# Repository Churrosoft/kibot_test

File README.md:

# kibot_test

export KICAD6_3DMODEL_DIR="/usr/share/kicad/3dmodels/"
export KICAD6_FOOTPRINT_DIR="/usr/share/kicad/footprints/"
export KICAD6_SYMBOL_DIR="/usr/share/kicad/symbols/"
export KICAD6_TEMPLATE_DIR="/usr/share/kicad/template/"

KICAD_USER_TEMPLATE_DIR	/home/fdsoftware/.local/share/kicad/6.0/template/	

KICAD6_3RD_PARTY	/home/fdsoftware/.local/share/kicad/6.0/3rdparty

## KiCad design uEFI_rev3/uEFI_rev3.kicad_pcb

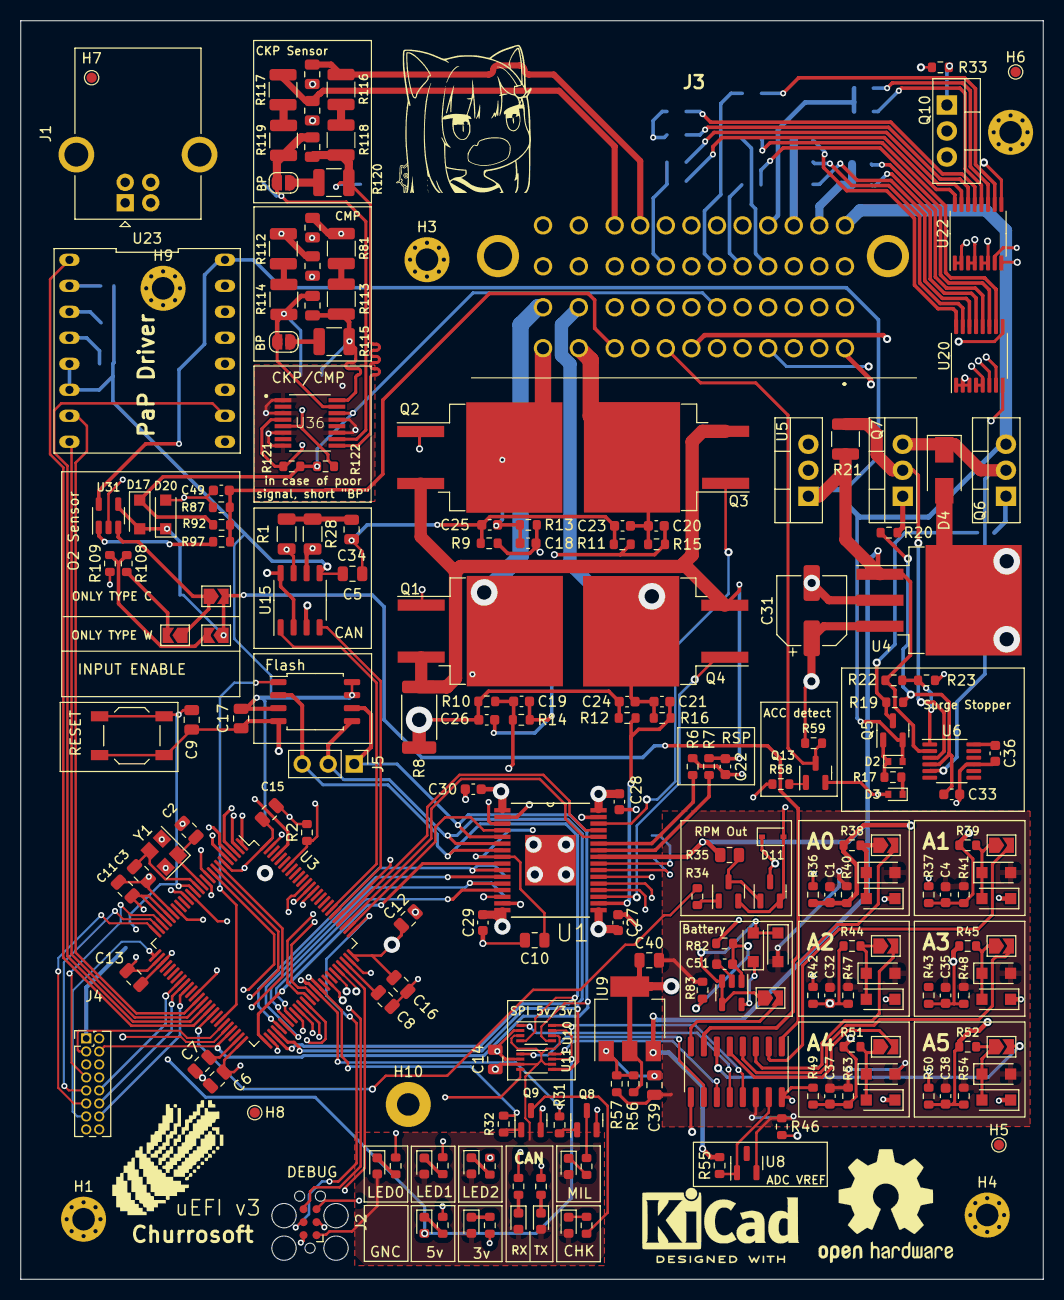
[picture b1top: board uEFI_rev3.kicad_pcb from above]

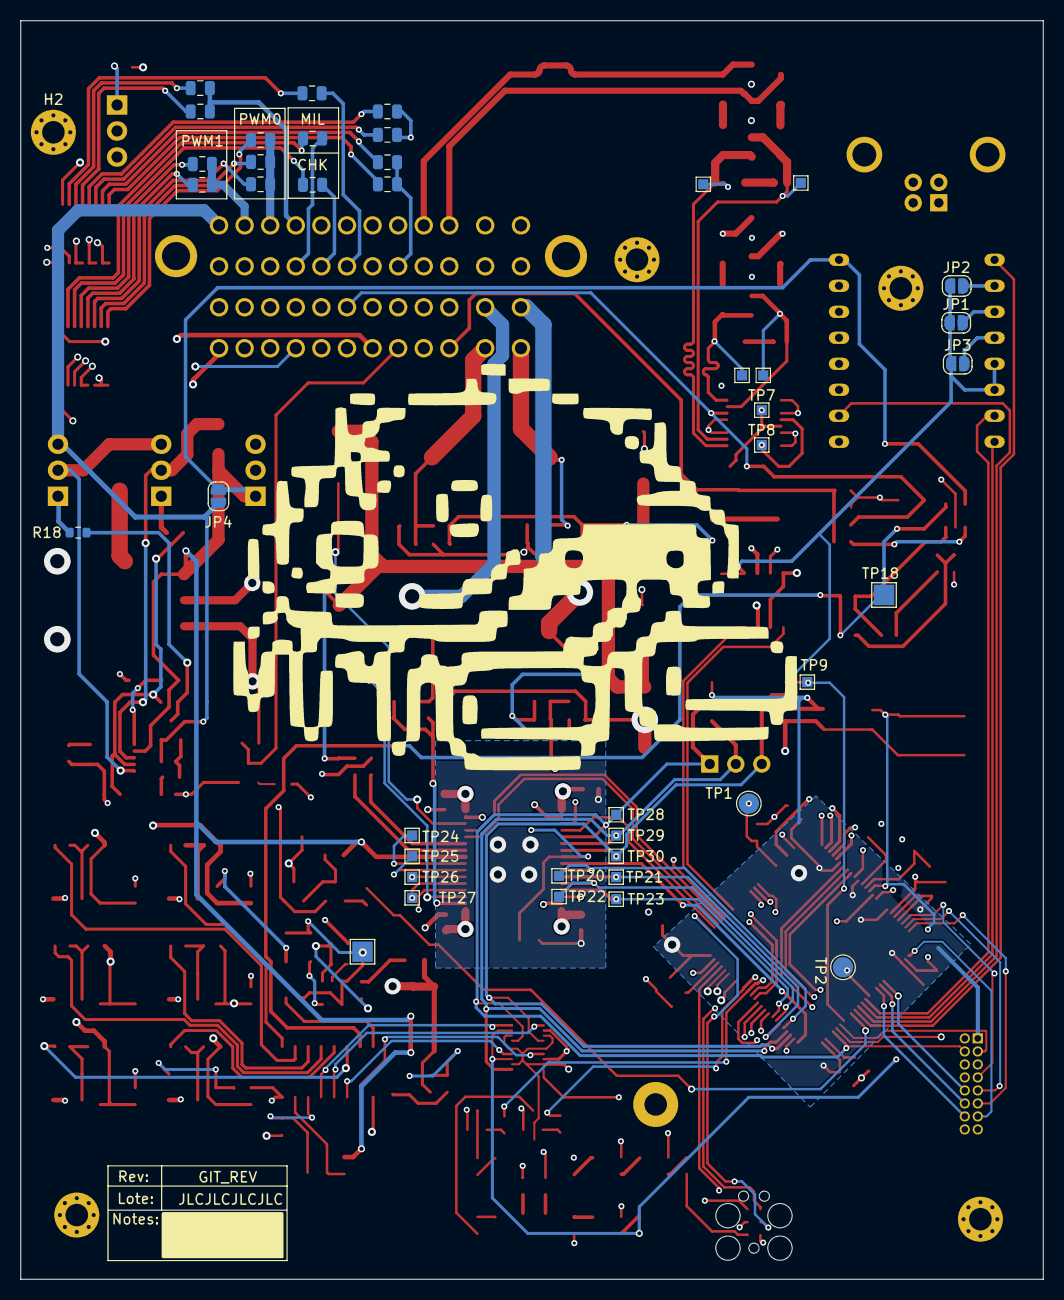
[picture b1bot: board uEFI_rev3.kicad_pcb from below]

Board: 4 copper layers, 99.9 x 123.0 mm, 258 parts (42 on the bottom side), 199 nets.

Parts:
C1, C4, C32, C35, C37, C38, C49, C51: 240pF; C_0603_1608Metric
C2, C3: 15pF; C_0805_2012Metric
C5, C9, C10, C11, C12, C13, C14, C15, C17, C39: 100nF; C_0805_2012Metric
C6: 1uF; C_0805_2012Metric
C7, C8: 2.2uF; C_0805_2012Metric
C16, C40: 4.7uF; C_0805_2012Metric
C18, C19, C20, C21, C22: 10pF; C_0603_1608Metric
C23, C24, C25, C26, C27, C28, C29, C30: 10nF; C_0603_1608Metric
C31: 100uF ±20% 35V; CP_Elec_6.3x7.7
C33: 47nF; C_0603_1608Metric
C34: 4.7nF; C_0805_2012Metric
C36: 0.1uF; C_0603_1608Metric
C52, C53, C54, C55, C56, C57: 0.01uF; C_0805_2012Metric
Churrosoft: SYM_Hot_Large; churro_new_v4
D1, D5, D6, D7, D8, D9, D10, D12, D13: LED; LED_0603_1608Metric
D2, D3: 1N4148; D_SOD-523
D4: SMAJ58CA; D_SMA
D11: MM3Z24VT1G; D_SOD-323
D15, D16, D17, D18, D19, D20, D21, D22, D23, D24, D25, D26, D27, D28, D29, D30: K26; D_SOD-123F
F1, F2, F3, F4, F5, F6, F7, F8, F9, F10, F11, F12, F13, F14: 750mA; Fuse_0805_2012Metric
H1, H2, H3, H4, H9: MountingHole; MountingHole_2.2mm_M2_Pad_Via
H5, H6, H7, H8: MountingHole; TestPoint_Pad_D1.0mm
H10: MountingHole; MountingHole_2.2mm_M2_Pad
J1: USB_B; USB_B_OST_USB-B1HSxx_Horizontal
J2: Tag connect; Tag-Connect_TC2030-IDC-FP_2x03_P1.27mm_Vertical
J3: 36638-0002; 366380002
J4: Conn_02x08_Odd_Even; PinHeader_2x08_P1.27mm_Vertical
J5: Conn_01x03; PinHeader_1x03_P2.54mm_Vertical
JP1, JP2, JP3, JP23, JP24: SolderJumper_2_Open; SolderJumper-2_P1.3mm_Open_RoundedPad1.0x1.5mm
JP4: Jumper_NO_Small; SolderJumper-2_P1.3mm_Open_RoundedPad1.0x1.5mm
JP5, JP6, JP7, JP8, JP9, JP10, JP12, JP15, JP17, JP18: Jumper_NC_Small; SolderJumper-2_P1.3mm_Open_TrianglePad1.0x1.5mm
LOGO1: Logo_Open_Hardware_Large; OSHW-Logo2_14.6x12mm_SilkScreen
Q1, Q2, Q3, Q4: ISL9V5045S3ST; TO-263-2
Q5, Q8, Q9, Q11: SS8050; SOT-23
Q6, Q7, Q10: IRF540N; TO-220-3_Vertical
Q12, Q13: AO3400A; SOT-23
R1, R28: R_Small; R_1206_3216Metric
R2, R55, R58, R59, R108, R109: 10k; R_0603_1608Metric
R3, R4, R5, R24, R25, R26, R27, R29, R30: 4.7k; R_0603_1608Metric
R6, R7: 100R; R_0603_1608Metric
R8: 0.02R; R_2512_6332Metric
R9, R10, R11, R12: 4.02k; R_0603_1608Metric
R13, R14, R15, R16: 36K; R_0603_1608Metric
R17: 10K 1/10W; R_0603_1608Metric
R18, R20, R33: 10R 1/10W; R_0603_1608Metric
R19: 1M 1/10W; R_0603_1608Metric
R21: 0.01R; R_1210_3225Metric
R22: 57.6K 1/10W; R_0603_1608Metric
R23: 4.99K 1/10W; R_0603_1608Metric
R31, R32, R34: 1k; R_0603_1608Metric
R35: 100k; R_0805_2012Metric
R36, R37, R42, R43, R49, R50, R92: 28.6k +-1%; R_0603_1608Metric
R38, R39, R44, R45, R51, R52, R97: 2.2k; R_0603_1608Metric
R40, R41, R47, R48, R53, R54, R87: 3.32k +-1%; R_0603_1608Metric
R46: 0; R_0603_1608Metric
R56: 750; R_0603_1608Metric
R57: 220; R_0603_1608Metric
R81, R112, R113, R114, R115, R116, R117, R118, R119, R120: 4.99K 1/2W; R_1210_3225Metric
R82: 100k 1/10W +-1%; R_0603_1608Metric
R83: 20k 1/10W +-1%; R_0603_1608Metric
R121, R122: R_Small; R_0603_1608Metric
SW1: SW_Push; SW_SPST_TL3342
SYM1: SYM_Hot_Small; KiCad-Logo2_6mm_SilkScreen
TP1: BOOT0; TestPoint_Pad_D2.0mm
TP2: BOOT1; TestPoint_Pad_D2.0mm
TP3, TP4, TP5, TP6, TP7, TP8, TP9, TP20, TP21, TP22, TP23, TP24, TP25, TP26, TP27, TP28, TP29, TP30: TestPoint; TestPoint_Pad_1.0x1.0mm
TP18, TP19: TestPoint; TestPoint_Pad_2.0x2.0mm
U1: MCZ33810EK; SOP65P1030X245-33N
U2: MCP3208; SOIC-16_3.9x9.9mm_P1.27mm
U3: STM32F407VGTx; LQFP-100_14x14mm_P0.5mm
U4: MIC2940A-3.3WU; TO-263-3_TabPin2
U5: MIC2940A-5.0WT; TO-220-3_Vertical
U6: LT4363IMS; MSOP-12_3x4mm_P0.65mm
U7: 25LCxxx; SOIC-8_5.275x5.275mm_P1.27mm
U8: LM4040DBZ-5; SOT-23
U9: AMS1117; SOT-223-3_TabPin2
U10, U11: TXS0102DCU; VSSOP-8_2.3x2mm_P0.5mm
U15: TJA1042T3118; HTSOP-8-1EP_3.9x4.9mm_P1.27mm_EP2.4x3.2mm
U20, U22: TPL7407LAPWR; TSSOP-16_4.4x5mm_P0.65mm
U23: PaP_Driver_v1; DIP-16_598_ELL
U27, U31: LM321; SOT-23-5
U36: MAX9926UAEE+; SOP63P602X175-16N
Y1: 25MHz; Crystal_SMD_3225-4Pin_3.2x2.5mm

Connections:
5V_ENABLE: R33.1, U3.16 (PC1)
+3V3: C5.1, C6.1, C10.1, C11.1, C12.1, C13.1, C14.1, C15.1, C16.1, C17.1, C31.1, D1.2 (A), D6.2 (A), D7.2 (A), D8.2 (A), D9.2 (A), D10.2 (A), D12.2 (A), D13.2 (A), J2.1, J4.1, JP1.1 (A), JP2.1 (A), JP3.1 (A), R59.1, U1.8 (VDD), U3.6 (VBAT), U3.11 (VDD), U3.19 (VDD), U3.21 (VREF+), U3.22 (VDDA), U3.28 (VDD), U3.50 (VDD), U3.75 (VDD), U3.100 (VDD), U4.3 (OUT), U7.3 (~WP), U7.7 (~HOLD), U7.8 (VCC), U10.3 (VCCA), U10.6 (OE), U11.3 (VCCA), U11.6 (OE), U15.5 (VIO), U23.5 (RESET), U23.6 (SLEEP)
+5C: C40.1, D15.1 (K), D16.1 (K), D21.1 (K), D22.1 (K), D25.1 (K), D26.1 (K), D27.1 (K), R36.2, R37.2, R42.2, R49.2, R50.2, R56.1, U2.16 (Vdd), U9.2 (VO), U27.5 (V+)
+5V: D5.2 (A), J4.2, Q10.3 (S), U5.3 (OUT), U10.7 (VCCB), U11.7 (VCCB), U15.3 (VCC)
+5VA: D17.1 (K), J3.A2, J3.B2, J3.C2, J3.D2, J3.E2, J3.F2, Q10.2 (D), R92.2, R121.1, R122.1, U36.14 (VCC)
+5VL: R55.1, U2.15 (Vref), U8.1 (K)
+12V: JP4.2, R21.1, R22.1, R35.1, R55.2, U1.25 (VPWR), U4.1 (IN), U5.1 (IN), U6.2 (OUT), U9.3 (VI), U20.9 (COM), U22.9 (COM), U23.16 (VMOT), U31.5 (V+)
+12VA: D2.2 (A), J3.A4, JP4.1, Q5.2 (E), Q6.3 (S), R82.2
/ACC_DET: R58.1, U3.80 (PC12)
/ADC_CS: U3.15 (PC0), U11.4 (A2)
/AUX_CS_1: J4.3, U3.45 (PE14)
/AUX_CS_2: J4.5, U3.46 (PE15)
/AUX_IN_1: J4.7, U3.23 (PA0)
/AUX_IN_2: J4.9, U3.24 (PA1)
/AUX_IN_3: J4.11, U3.25 (PA2)
/AUX_IN_4: J4.13, U3.26 (PA3)
/AUX_OUT_1: J4.10, U3.33 (PC4)
/AUX_OUT_2: J4.12, U3.34 (PC5)
/AUX_OUT_3: J4.14, U3.35 (PB0)
/CAN1_RX: U3.81 (PD0), U15.4 (RXD)
/CAN1_TX: U3.82 (PD1), U15.1 (TXD)
/CHK: Q9.3 (C), R30.2
/CHK_OUT: R32.1, U3.66 (PC9), U20.6 (IN6)
/CKP: R121.2, TP8.1, U3.63 (PC6), U36.4 (COUT1)
/CKP/CMP_sensors/IN1+: C54.1, R113.2, R115.1, TP4.1, U36.16 (IN1+)
/CKP/CMP_sensors/IN1-: C54.2, JP23.1 (A), R114.2, TP5.1, U36.15 (IN1-)
/CKP/CMP_sensors/IN2+: C57.2, JP24.1 (A), R119.2, TP6.1, U36.10 (IN2-)
/CKP/CMP_sensors/IN2-: C57.1, R118.2, R120.1, TP3.1, U36.9 (IN2+)
/CMP: R122.2, TP7.1, U3.64 (PC7), U36.5 (COUT2)
/ECN1: TP24.1, U1.24 (GIN0), U3.59 (PD12)
/ECN2: TP25.1, U1.23 (GIN1), U3.60 (PD13)
/ECN3: TP26.1, U1.22 (GIN2), U3.61 (PD14)
/ECN4: TP27.1, U1.21 (GIN3), U3.62 (PD15)
/INY1: TP20.1, U1.10 (DIN0), U3.55 (PD8)
/INY2: TP21.1, U1.11 (DIN1), U3.56 (PD9)
/INY3: TP22.1, U1.12 (DIN2), U3.57 (PD10)
/INY4: TP23.1, U1.13 (DIN3), U3.58 (PD11)
/LED0: R25.2, U3.7 (PC13)
/LED1: R26.2, U3.8 (PC14)
/LED2: R27.2, U3.9 (PC15)
/LED_CAN_RX: R24.2, U3.87 (PD6)
/LED_CAN_TX: R5.2, U3.88 (PD7)
/MEMORY_CS: TP9.1, U3.44 (PE13), U7.1 (~CS)
/MIL: Q8.3 (C), R29.2
/MIL_OUT: R31.1, U3.65 (PC8), U20.7 (IN7)
/MTR_DIR: U3.39 (PE8), U23.8 (DIR)
/MTR_ENABLE: U3.41 (PE10), U23.1 (ENABLE)
/MTR_FAULT: U3.40 (PE9), U23.10 (FAULT)
/MTR_STEP: U3.38 (PE7), U23.7 (STEP)
/NRST: C9.2, J2.3, SW1.1, U3.14 (NRST)
/PMIC_CS: U1.4 (~CS), U3.77 (PA15)
/PMIC_ENABLE: U1.9 (~OUTEN), U3.51 (PB12)
/PMIC_MAXI: U1.29 (MAXI), U3.79 (PC11)
/PMIC_NOMI: U1.28 (NOMI), U3.78 (PC10)
/PMIC_SPARK: U1.20 (~SPKDUR), U3.52 (PB13)
/PWM/Relays/CHECK_ENGINE: F14.1, U20.11 (OUT6)
/PWM/Relays/MIL_OUT: F13.1, U20.10 (OUT7)
/PWM/Relays/R3_OUT: F12.1, U22.10 (OUT7)
/RPM_OUT: R34.1, U3.42 (PE11)
/RSN: R6.2, U1.27 (RSN)
/RSP: R7.2, U1.26 (RSP)
/R_AAC: U3.3 (PE4), U22.1 (IN1), U22.2 (IN2)
/R_ECN_INY: U3.1 (PE2), U22.5 (IN5), U22.6 (IN6)
/R_GNC_GLP: U3.2 (PE3), U22.3 (IN3), U22.4 (IN4)
/R_LMB: U3.97 (PE0), U22.7 (IN7)
/SPI2_MISO: J4.6, J5.3, TP30.1, U1.7 (SO), U3.53 (PB14), U7.2 (MISO), U10.4 (A2)
/SPI2_MOSI: J4.8, J5.2, TP29.1, U1.6 (SI), U3.54 (PB15), U7.5 (MOSI), U11.5 (A1)
/SPI2_SCK: J4.4, J5.1, TP28.1, U1.5 (SCLK), U3.47 (PB10), U7.6 (SCK), U10.5 (A1)
/SYS_SWCLK: J2.4, U3.76 (PA14)
/SYS_SWDIO: J2.2, U3.72 (PA13)
/SYS_SWO: J2.6, U3.89 (PB3)
/Sensores/CH0: D16.2 (A), D19.1 (K), JP5.1, R38.1
/Sensores/CH1: D15.2 (A), D18.1 (K), JP6.1, R39.1
/Sensores/CH2: D21.2 (A), D23.1 (K), JP7.1, R44.1
/Sensores/CH3: D22.2 (A), D24.1 (K), JP8.1, R45.1
/Sensores/CH4: D26.2 (A), D29.1 (K), JP9.1, R51.1
/Sensores/CH5: D27.2 (A), D30.1 (K), JP10.1, R52.1
/Sensores/CH6: D17.2 (A), D20.1 (K), JP15.2, JP18.1, TP18.1, U2.7 (CH6), U31.4
/Sensores/CH7: D25.2 (A), D28.1 (K), JP12.1, TP19.1, U27.3 (-), U27.4
/Sensores/CLK: U2.13 (CLK), U10.8 (B1)
/Sensores/CS: U2.10 (~CS/SHDN), U11.1 (B2)
/Sensores/DIN: U2.11 (Din), U11.8 (B1)
/Sensores/DOUT: U2.12 (Dout), U10.1 (B2)
/Sheet5FA9324A/FB0: C18.2, R9.2, R13.1, U1.2 (FB0)
/Sheet5FA9324A/FB1: C19.2, R10.2, R14.1, U1.15 (FB1)
/Sheet5FA9324A/FB2: C20.2, R11.2, R15.1, U1.31 (FB2)
/Sheet5FA9324A/FB3: C21.2, R12.2, R16.1, U1.18 (FB3)
/Sheet5FA9324A/GD0: Q2.1 (G), U1.3 (GD0)
/Sheet5FA9324A/GD1: Q1.1 (G), U1.14 (GD1)
/Sheet5FA9324A/GD2: Q3.1 (G), U1.30 (GD2)
/Sheet5FA9324A/GD3: Q4.1 (G), U1.19 (GD3)
/TIM9_CH1: U3.4 (PE5), U20.1 (IN1), U20.2 (IN2), U20.3 (IN3)
/TIM9_CH2: U3.5 (PE6), U20.4 (IN4), U20.5 (IN5)
/USB_D+: J1.3 (D+), U3.71 (PA12)
/USB_D-: J1.2 (D-), U3.70 (PA11)
/VBUS: J1.1 (VBUS), U3.68 (PA9)
A1: D11.1 (K), J3.A1, Q12.3 (D)
B1: C1.1, J3.B1, R36.1, R38.2, R40.1
B4: F10.2, F11.2, J3.B4
C1: C4.1, J3.C1, R37.1, R39.2, R41.1
C4: F5.2, F7.2, F8.2, J3.C4
CAN+: J3.J2, R1.2, U15.7 (CANH)
CAN-: J3.K2, R28.2, U15.6 (CANL)
CKP+: C55.1, J3.K4, R117.1
CKP-: C56.1, J3.J4, R116.1
CMP+: C53.1, J3.K3, R81.1
CMP-: C52.1, J3.J3, R112.1
D1: C32.1, J3.D1, R42.1, R44.2, R47.1
D3: F13.2, J3.D3
D4: F2.2, F4.2, J3.D4
E1: C35.1, J3.E1, R43.1, R45.2, R48.1
E3: F14.2, J3.E3
E4: J3.E4, U23.14 (B2)
F1: C37.1, J3.F1, R49.1, R51.2, R53.1
F3: F12.2, J3.F3
F4: J3.F4, U23.13 (B1)
G1: C38.1, J3.G1, R50.1, R52.2, R54.1
G3: F6.2, F9.2, J3.G3
G4: J3.G4, U23.12 (A1)
GND: C2.2, C3.2, C5.2, C6.2, C7.2, C8.2, C9.1, C10.2, C11.2, C12.2, C13.2, C14.2, C15.2, C16.2, C17.2, C22.1, C23.2, C24.2, C25.2, C26.2, C27.1, C28.1, C29.1, C30.1, C31.2, C33.2, C34.2, C36.2, C49.2, C52.2, C53.2, C55.2, C56.2, D3.2 (A), D4.2 (A2), D11.2 (A), D20.2 (A), J1.4 (GND), J1.5 (Shield), J2.5, J3.A3, J3.B3, J3.C3, J3.G2, J3.H2, J3.MH1, J3.MH2, J4.15, J4.16, Q8.2 (E), Q9.2 (E), Q11.2 (E), Q12.2 (S), Q13.2 (S), R2.2, R3.2, R4.2, R6.1, R8.2, R9.1, R10.1, R11.1, R12.1, R23.1, R46.2, R87.2, R109.1, SW1.2, U1.33 (GND), U2.9 (DGND), U3.10 (VSS), U3.20 (VSSA), U3.27 (VSS), U3.74 (VSS), U3.99 (VSS), U4.2 (GND), U5.2 (GND), U6.9 (GND), U7.4 (GND), U10.2 (GND), U11.2 (GND), U15.2 (GND), U15.8 (STB), U20.8 (GND), U22.8 (GND), U23.9 (GND), U23.15 (GND), U31.2 (V-), U36.1 (INT_THRS1), U36.3 (BIAS1), U36.6 (BIAS2), U36.8 (INT_THRS2), U36.11 (GND), U36.13 (ZERO_EN), Y1.2, Y1.4
GNDA: C1.2, C4.2, C32.2, C35.2, C37.2, C38.2, C39.2, C40.2, C51.2, D18.2 (A), D19.2 (A), D23.2 (A), D24.2 (A), D28.2 (A), D29.2 (A), D30.2 (A), R40.2, R41.2, R46.1, R47.2, R48.2, R53.2, R54.2, R57.1, R83.2, U2.14 (AGND), U8.2 (A), U27.2 (V-)
H1: J3.H1, Q13.3 (D), R59.2
H3: F1.2, F3.2, J3.H3
H4: J3.H4, U23.11 (A2)
K1: C49.1, J3.K1, R87.1, R92.1, R97.2
L1: C20.1, C23.1, J3.L1, Q3.2 (C), R15.2
L2: C21.1, C24.1, J3.L2, Q4.2 (C), R16.2
L3: C27.2, J3.L3, U1.17 (OUT3)
L4: C28.2, J3.L4, U1.32 (OUT2)
M1: C18.1, C25.1, J3.M1, Q2.2 (C), R13.2
M2: C19.1, C26.1, J3.M2, Q1.2 (C), R14.2
M3: C29.2, J3.M3, U1.16 (OUT1)
M4: C30.2, J3.M4, U1.1 (OUT0)
unnamed: C7.1, U3.49 (VCAP_1)
unnamed: C8.1, U3.73 (VCAP_2)
unnamed: C22.2, Q1.3 (E), Q2.3 (E), Q3.3 (E), Q4.3 (E), R7.1, R8.1
unnamed: C33.1, R19.1, R20.2, U6.4 (GATE)
unnamed: C34.1, R1.1, R28.1
unnamed: C36.1, U6.12 (TMR)
unnamed: C39.1, R56.2, R57.2, U9.1 (ADJ)
unnamed: C51.1, R82.1, R83.1, U27.1 (+)
unnamed: D1.1 (K), R3.1
unnamed: D2.1 (K), Q5.1 (B), R17.1
unnamed: D3.1 (K), R17.2
unnamed: D4.1 (A1), Q6.2 (D), Q7.3 (S), U6.5 (VCC)
unnamed: D5.1 (K), R4.1
unnamed: D6.1 (K), R5.1
unnamed: D7.1 (K), R24.1
unnamed: D8.1 (K), R25.1
unnamed: D9.1 (K), R26.1
unnamed: D10.1 (K), R27.1
unnamed: D12.1 (K), R29.1
unnamed: D13.1 (K), R30.1
unnamed: F1.1, U22.15 (OUT2)
unnamed: F2.1, U22.11 (OUT6)
unnamed: F3.1, U22.16 (OUT1)
unnamed: F4.1, U22.12 (OUT5)
unnamed: F5.1, U20.14 (OUT3)
unnamed: F6.1, U22.13 (OUT4)
unnamed: F7.1, U20.15 (OUT2)
unnamed: F8.1, U20.16 (OUT1)
unnamed: F9.1, U22.14 (OUT3)
unnamed: F10.1, U20.12 (OUT5)
unnamed: F11.1, U20.13 (OUT4)
unnamed: JP1.2 (B), U23.3 (M1)
unnamed: JP2.2 (B), U23.2 (M0)
unnamed: JP3.2 (B), U23.4 (M2)
unnamed: JP5.2, U2.1 (CH0)
unnamed: JP6.2, U2.2 (CH1)
unnamed: JP7.2, U2.3 (CH2)
unnamed: JP8.2, U2.4 (CH3)
unnamed: JP9.2, U2.5 (CH4)
unnamed: JP10.2, U2.6 (CH5)
unnamed: JP12.2, U2.8 (CH7)
unnamed: JP15.1, JP17.1, U31.3 (-)
unnamed: JP17.2, R108.2
unnamed: JP18.2, R108.1, R109.2
unnamed: JP23.2 (B), R115.2
unnamed: JP24.2 (B), R120.2
unnamed: Q5.3 (C), R18.2, R19.2
unnamed: Q6.1 (G), R18.1
unnamed: Q7.1 (G), R20.1
unnamed: Q7.2 (D), R21.2, U6.3 (SNS)
unnamed: Q8.1 (B), R31.2
unnamed: Q9.1 (B), R32.2
unnamed: Q10.1 (G), R33.2
unnamed: Q11.1 (B), R34.2
unnamed: Q11.3 (C), Q12.1 (G), R35.2
unnamed: Q13.1 (G), R58.2
unnamed: R2.1, TP1.1, U3.94 (BOOT0)
unnamed: R22.2, R23.2, U6.1 (FB)
unnamed: R97.1, U31.1 (+)
unnamed: R112.2, R114.1
unnamed: R81.2, R113.1
unnamed: R116.2, R118.1
unnamed: R117.2, R119.1
unnamed: TP2.1, U3.37 (PB2)
OSC_IN: C2.1, U3.12 (PH0), Y1.1
OSC_OUT: C3.1, U3.13 (PH1), Y1.3

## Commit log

2022-03-24 test
2022-03-26 fix run command
2022-03-26 added kicad cfg file
2022-03-27 get kibot from repo and install
2022-03-27 update var step
2022-03-28 ooops le erre de paquetito
2022-03-28 build all kibot deeps from main
2022-03-28 install kibot with pip3
2022-03-28 test _k6 image
2022-03-28 added pcb library
2022-03-28 fix uri lib
2022-03-28 added xvfbwrapper
2022-03-28 added debug output
2022-03-28 added xvfb/xvfbwrapper
2022-03-28 added recordmydesktop for debug
2022-03-28 remove .sch
2022-03-28 update release workflow
2022-03-28 fix schema file
2022-03-28 test v2_k6 image
2022-03-28 fix release k6
2022-03-28 remove variant: rotated on jlcpcb kibot
2022-03-28 custom filters broken?
2022-03-28 added Boardview to docs workflow
2022-03-28 skip jlcpcb stage
2022-03-28 added kicad install
2022-03-29 update Preflight
2022-03-29 asddsa

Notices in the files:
uEFI_rev3/uEFI_rev3.kicad_pcb:
MIT Licence
